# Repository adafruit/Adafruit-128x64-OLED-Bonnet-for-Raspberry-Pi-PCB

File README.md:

## Adafruit 128x64 OLED Bonnet for Raspberry Pi PCB

<a href="http://www.adafruit.com/products/3531"><br/>
Click here to purchase one from the Adafruit shop</a>

PCB files for the Adafruit 128x64 OLED Bonnet for Raspberry Pi. Format is EagleCAD schematic and board layout

For more details, check out the product page at
* http://www.adafruit.com/product/3531

### Description

If you'd like a compact display, with buttons and a joystick - we've got what you're looking for. The Adafruit 128x64 OLED Bonnet for Raspberry Pi is the big sister to our mini PiOLED add-on. This version has 128x64 pixels (instead of 128x32) and a much larger screen besides. With the OLED display in the center, we had some space on either side so we added a 5-way joystick and two pushbuttons. Great for when you want to have a control interface for your project.

These displays are small, only about 1.3" diagonal, but very readable due to the high contrast of an OLED display. This screen is made of 128x64 individual white OLED pixels and because the display makes its own light, no backlight is required. This reduces the power required to run the OLED and is why the display has such high contrast; we really like this miniature display for its crispness!

Please note that this display is too small to act as a primary display for the Pi (e.g. it can't act like or display what would normally be on the HDMI screen). Instead, we recommend using pygame for drawing or writing text.

Using the display and controls in python is very easy, we have a library ready-to-go for the SSD1306 OLED chipset and the joystick/buttons are connected to GPIO pins on the Pi. Our example code allows you to draw images, text, whatever you like, using the Python imaging library. We also have example code for using the joystick/buttons/OLED together. Our tests showed 15 FPS update rates so you can do animations or simple video.

Comes completely pre-assembled and tested so you don't need to do anything but plug it in and install our Python code! Works with any Raspberry Pi computer, including the original Pi 1, B+, Pi 2, Pi 3 and Pi Zero.

### License

Adafruit invests time and resources providing this open source design, please support Adafruit and open-source hardware by purchasing products from [Adafruit](https://www.adafruit.com)!

Designed by Limor Fried/Ladyada for Adafruit Industries.

Creative Commons Attribution/Share-Alike, all text above must be included in any redistribution. See license.txt for additional details.

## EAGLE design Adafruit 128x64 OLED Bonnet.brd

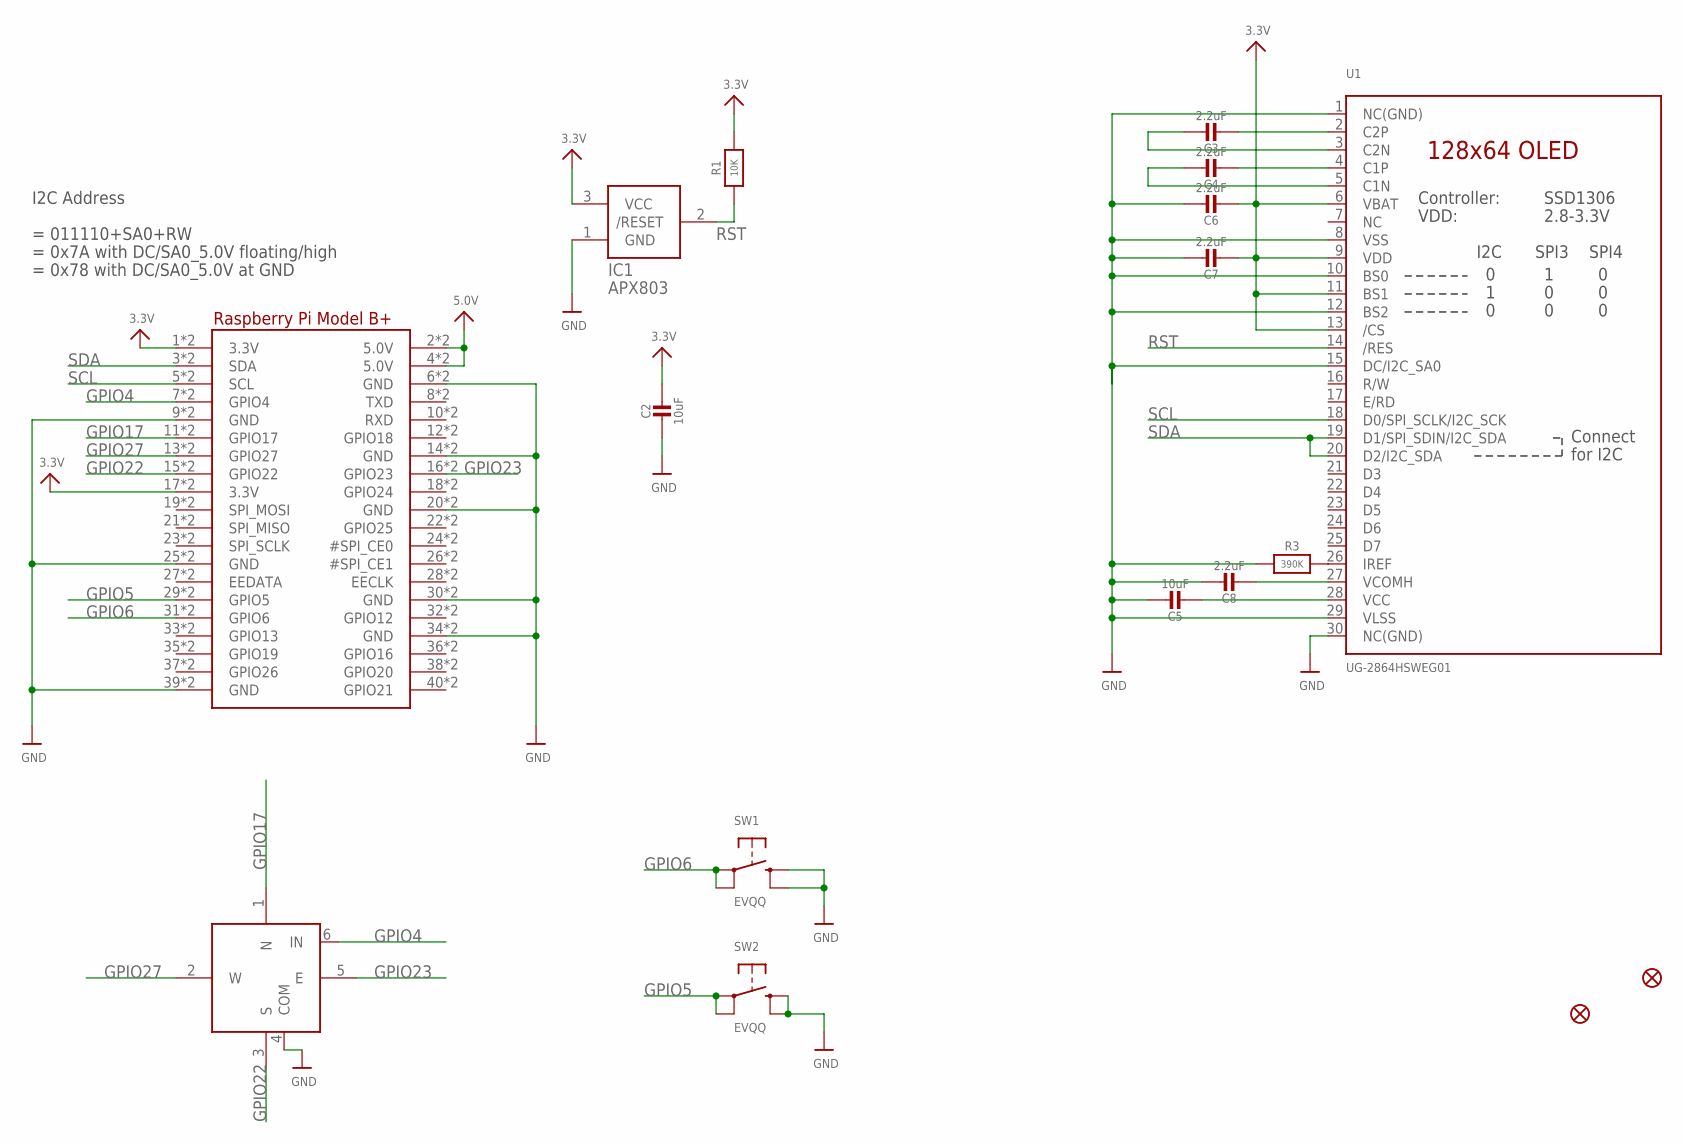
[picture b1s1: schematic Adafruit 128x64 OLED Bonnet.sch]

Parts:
C2, C5: 10uF; 0805-NO
C3, C4, C6, C7, C8: 2.2uF; 0805-NO
FID1, FID2: FIDUCIAL_1MM
IC1: APX803; SOT23
R1: 10K; 0805-NO
R3: 390K; 0805-NO
RPI1: RASPBERRYPI_BPLUS_BONNET_THMSMT; PI_BONNET_THMSMT
SW1, SW2: EVQQ; EVQ-Q2_SMALLER
SW3: NAVSWITCHSKQUABAUE010; SKQUBAE010
U1: UG-2864HSWEG01; UG-2864HSWEG01_1.3_WRAPAROUND

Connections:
3.3V: C2.1, C6.2, C7.2, IC1.3 (VCC), R1.2, RPI1.1 (3.3V), RPI1.17 (3.3V), RPI1.S1 (3.3V), RPI1.S17 (3.3V), U1.6 (VBAT), U1.9 (VDD), U1.11 (BS1), U1.13 (/CS)
5.0V: RPI1.2 (5.0V), RPI1.4 (5.0V), RPI1.S2 (5.0V), RPI1.S4 (5.0V)
GND: C2.2, C5.1, C6.1, C7.1, C8.1, IC1.1 (GND), R3.1, RPI1.6 (GND), RPI1.9 (GND), RPI1.14 (GND), RPI1.20 (GND), RPI1.25 (GND), RPI1.30 (GND), RPI1.34 (GND), RPI1.39 (GND), RPI1.S6 (GND), RPI1.S9 (GND), RPI1.S14 (GND), RPI1.S20 (GND), RPI1.S25 (GND), RPI1.S30 (GND), RPI1.S34 (GND), RPI1.S39 (GND), SW1.B (S), SW1.B' (S1), SW2.B (S), SW2.B' (S1), SW3.4 (COM), U1.1 (NC(GND)), U1.8 (VSS), U1.10 (BS0), U1.12 (BS2), U1.15 (DC/I2C_SA0), U1.29 (VLSS), U1.30 (NC(GND))
GPIO4: RPI1.7 (GPIO4), RPI1.S7 (GPIO4), SW3.6 (IN)
GPIO5: RPI1.29 (GPIO5), RPI1.S29 (GPIO5), SW2.A, SW2.A' (P1)
GPIO6: RPI1.31 (GPIO6), RPI1.S31 (GPIO6), SW1.A, SW1.A' (P1)
GPIO17: RPI1.11 (GPIO17), RPI1.S11 (GPIO17), SW3.1 (N)
GPIO22: RPI1.15 (GPIO22), RPI1.S15 (GPIO22), SW3.3 (S)
GPIO23: RPI1.16 (GPIO23), RPI1.S16 (GPIO23), SW3.5 (E)
GPIO27: RPI1.13 (GPIO27), RPI1.S13 (GPIO27), SW3.2 (W)
unnamed: R3.2, U1.26 (IREF)
unnamed: C3.2, U1.2 (C2P)
unnamed: C3.1, U1.3 (C2N)
unnamed: C4.2, U1.4 (C1P)
unnamed: C4.1, U1.5 (C1N)
unnamed: C5.2, U1.28 (VCC)
unnamed: C8.2, U1.27 (VCOMH)
RST: IC1.2 (/RESET), R1.1, U1.14 (/RES)
SCL: RPI1.5 (SCL), RPI1.S5 (SCL), U1.18 (D0/SPI_SCLK/I2C_SCK)
SDA: RPI1.3 (SDA), RPI1.S3 (SDA), U1.19 (D1/SPI_SDIN/I2C_SDA), U1.20 (D2/I2C_SDA)

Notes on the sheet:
= 011110+SA0+RW
= 0x7A with DC/SA0_5.0V floating/high
= 0x78 with DC/SA0_5.0V at GND
I2C Address

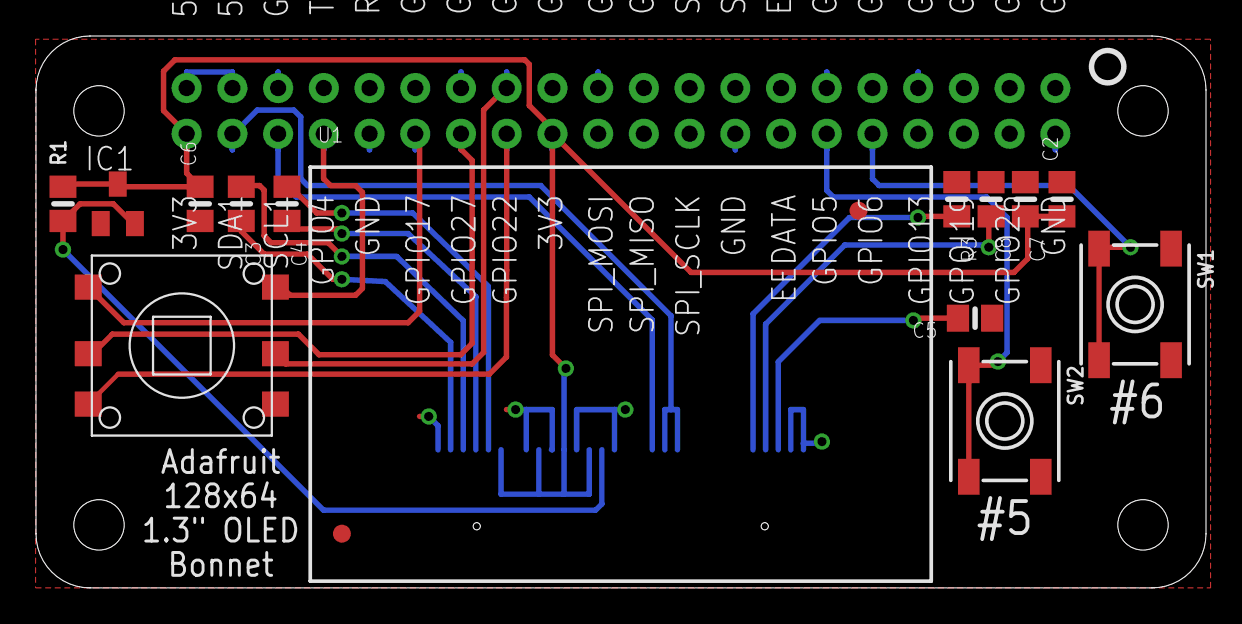
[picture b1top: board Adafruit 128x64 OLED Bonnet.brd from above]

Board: 2 copper layers, 65.0 x 30.7 mm, 18 parts (0 on the bottom side), 20 nets.

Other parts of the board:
U$2: PCBFEAT-REV-040

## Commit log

2017-06-09 init
